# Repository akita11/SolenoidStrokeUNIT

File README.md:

# SolenoidStokeUNIT

ソレノイドのストローク位置によってインダクタンスが変化し、PWM制御時の電流波形が変化することを利用して、ソレノイドのPWM制御とストローク位置の計測（推定）を同時に行うための回路です。

**【注意：重要】**
実際の制御・計測の動作には、ソレノイドごとに特性の計測を行う必要があり、また特性の個体差、温度特性なども考慮する必要があります。そのため、**「これを使ってサンプルプログラムを書き込めば間違いなく動作する（制御ができる）」というものではなく、あくまでもこの原理検証の実験のための回路**ということをご理解ください。測定原理やサンプルプログラムは[こちら](https://github.com/akita11/SolenoidStrokeMeasureControl)に適宜まとめて更新していきます。

## 使い方

オレンジ色のコネクタ(VH3.96-4p)に、ソレノイド用の電源とソレノイドを接続します。M5Stackの[BAVGソケット](https://www.switch-science.com/products/7234)を使うと、電源は2.1mmプラグ、負荷はスプリング端子で接続できて便利です。

Grove端子にUART通信元（M5Stack等のマイコンやUSBシリアル変換器）を接続し、本UNITに対してコマンド送信や結果の受信を行います。Grove端子の信号は、"RXD(受信) / TXD(送信) / VDD(+5V) / GND"の順です。ここでRXDとTXDの「主語」は本UNITです。つまり本UNITの"RXD"は、UART送信元の送信(TX)に接続します。（なおM5StackのPortCのTX/RXはこの順序ですのでそのまま接続できます）

### コマンド

コマンドは、基本的に、「コマンドを表す1文字 + 引数（10進数表記：ないものもある） + <CR> or <LF>」の形式です。各コマンドの成功時には'S'と'P'以外では指定された設定が返され、定義されていないコマンドでは'?'が返されます。

- 'S' : 測定開始（引数なし）：後述の形式で測定データが送出されます
- 'P' : 測定停止（引数なし）
- 'D' : PWM ON時間の設定（引数：PWM ON時間（単位は0.8us））
- 'T' : PWM ON時間の設定（引数：PWM周期（単位は0.8us））
- '0' : PWM ONから第1サンプリング点までの時間（引数：PWM周期（単位は0.8us））
- '1' : PWM ONから第2サンプリング点までの時間（引数：PWM周期（単位は0.8us））
- 'C' : 内部蓄積回数（引数：回）

### 送出データの形式

AAAABBBB + <CR> + <LF>

- AAAA : 第1サンプリング点の電圧値（10進数4桁）：0=0V, 1023=5V
- BBBB : 第2サンプリング点の電圧値（10進数4桁）：0=0V, 1023=5V

### 増幅率の調整

ソレノイドの駆動電流を0.2Ωの抵抗で電圧変換し、それをオペアンプ（非反転増幅回路）で増幅して"ADC"端子に出力しています。その増幅率は、用いるソレノイド・電源電圧からきまる駆動電流にあわせて、適切な範囲に調整する必要があります。"ADC"端子の波形をオシロ等で計測し、用いるマイコンのADCの入力電圧範囲に収まるように増幅率を調整します。増幅率は基板裏面のハンダジャンパJP3/JP4JP5で調整できます。（JP3は初期状態でONになっていますので、OFFにする場合はパターンをカットしてください）

- JP3/JP4/JP5=ON/OFF/OFF : 101倍
- JP3/JP4/JP5=ON/ON/OFF : 39倍
- JP3/JP4/JP5=ON/OFF/ON : 20倍
- JP3/JP4/JP5=ON/ON/ON : 16倍
- JP3/JP4/JP5=OFF/OFF/OFF : R1にとりつける抵抗から決まる倍率（(R1÷1[kΩ]+1)倍）

## 測定原理

ソレノイドは電気回路的にはインダクタで、そのインダクタンスはストローク（プランジャ）位置で変化します。そのためON時の充電電流の波形は、ストローク位置で変化します。ただし充電開始時の電流はOFF期間中の放電特性できまるため、ゼロからとは限りません。またPWMのON時間（PWMのデューティー比）によっても波形は変化します。

ソレノイドによっては、ON後の2箇所の時点（例えば100us後と700us後）での電流の差が、PWMのON時間（PWMのデューティー比）ごとにストローク位置に伴って変化するため、与えているPWM ON時間とその電流差から、ストローク位置を計測（推定）することができます。具体的には、PWM ON後に電流が徐々に増加するところの2点（第1・第2サンプリング点）の電圧から、あらかじめ学習させた深層学習CNNモデルによってソレノイドのストローク位置とコイル温度を求めることができます。詳細はarXivの[論文(1)](https://arxiv.org/abs/2405.11721)と[論文(2)](https://arxiv.org/abs/2411.07270)にまとめてあります。

ただしソレノイドによっては、この電流差がストロークによってほとんど変化しないため、この方法では位置を計測することができません。そのため、複数点の電流の計測値から、予め計測した位置と電流値との差（の総和）が最小となるように反復計算で位置を求めるアルゴリズムを開発中です。まだ安定性や精度の検証は不十分ですが、参考用に上記GitHubにいくつかのソレノイドのCNNモデルと、それをESP32(M5Stack等)で実行するためのソースコードをおいてあります。

現在、SSBH-0830-02用の推定モデルとそれを使った位置制御(Control_ESP32/)をおいてあります。上記GitHubの生活をREADME.mdは別の計測制御(SolenoidStokeMeasureControlUNIT)用の情報が書いてありますが、この位置制御のソースコードは、本ユニット用のものです。

## Author

Junichi Akita (akita@ifdl.jp, @akita11)

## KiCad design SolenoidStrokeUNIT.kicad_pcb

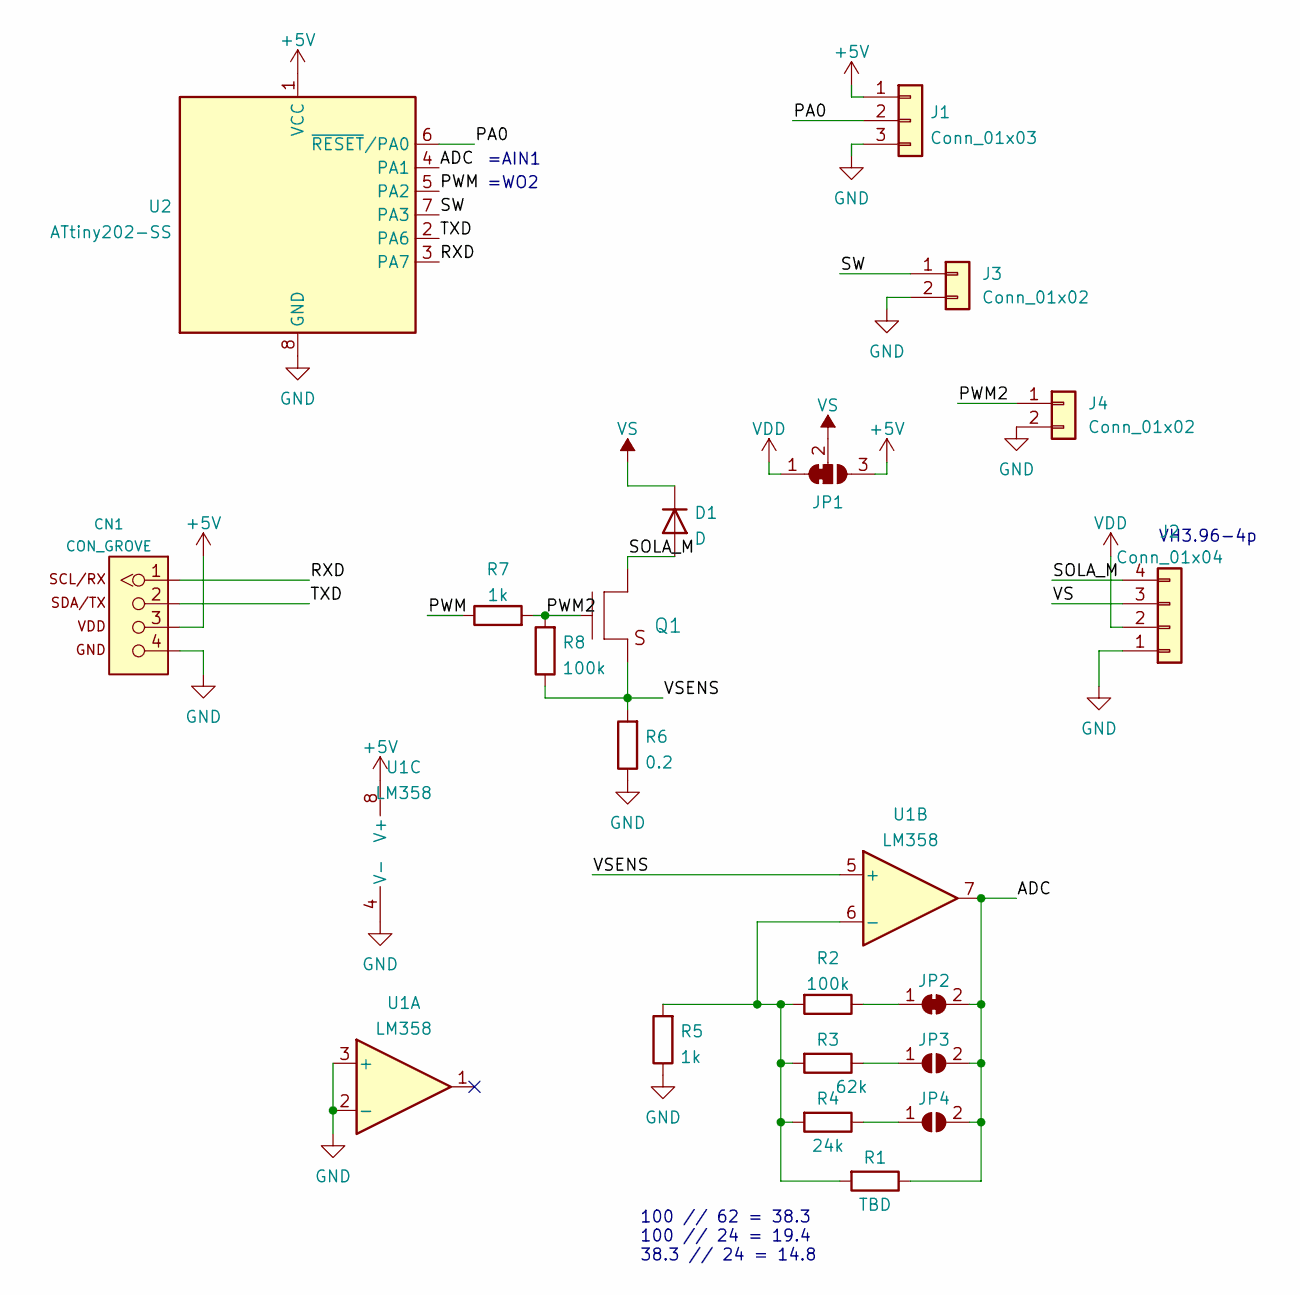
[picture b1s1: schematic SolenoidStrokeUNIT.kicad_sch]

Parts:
CN1: CON_GROVE; CON_GROVE_H
D1: D; D_SOD-123F
J1: Conn_01x03; PinSocket_1x03_P2.54mm_Vertical
J2: Conn_01x04; JST_VH_S4P-VH_1x04_P3.96mm_Horizontal
J3, J4: Conn_01x02; PinSocket_1x02_P2.54mm_Vertical
JP1: SolderJumper_3_Bridged12; SolderJumper-3_P1.3mm_Bridged2Bar12_Pad1.0x1.5mm
JP2: SolderJumper_2_Bridged; SolderJumper-2_P1.3mm_Bridged_Pad1.0x1.5mm
JP3, JP4: SolderJumper_2_Open; SolderJumper-2_P1.3mm_Open_Pad1.0x1.5mm
Q1: TR_NMOS_IRLML6344; SOT-23
R1: TBD; R_Axial_DIN0207_L6.3mm_D2.5mm_P2.54mm_Vertical
R2, R8: 100k; R_0603_1608Metric
R3: 62k; R_0603_1608Metric
R4: 24k; R_0603_1608Metric
R5, R7: 1k; R_0603_1608Metric
R6: 0.2; R_1206_3216Metric
U1: LM358; SO-8_3.9x4.9mm_P1.27mm
U2: ATtiny202-SS; SOIC-8_3.9x4.9mm_P1.27mm

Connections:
+5V: CN1.3, J1.1, JP1.3 (B), U1.8 (V+), U2.1 (VCC)
/ADC: JP2.2 (B), JP3.2 (B), JP4.2 (B), R1.1, U1.7, U2.4 (PA1)
/PA0: J1.2, U2.6 (~RESET/PA0)
/PWM: R7.1, U2.5 (PA2)
/PWM2: J4.1, Q1.1 (G), R7.2, R8.2
/RXD: CN1.1, U2.3 (PA7)
/SOLA_M: D1.2 (A), J2.4, Q1.3 (D)
/SW: J3.1, U2.7 (PA3)
/TXD: CN1.2, U2.2 (PA6)
/VSENS: Q1.2 (S), R6.2, R8.1, U1.5 (+)
GND: CN1.4, J1.3, J2.1, J3.2, J4.2, R5.1, R6.1, U1.2 (-), U1.3 (+), U1.4 (V-), U2.8 (GND)
unnamed: JP2.1 (A), R2.1
unnamed: JP3.1 (A), R3.1
unnamed: JP4.1 (A), R4.1
unnamed: R1.2, R2.2, R3.2, R4.2, R5.2, U1.6 (-)
VDD: J2.2, JP1.1 (A)
VS: D1.1 (K), J2.3, JP1.2 (C)

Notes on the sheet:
100 // 62 = 38.3 100 // 24 = 19.4 38.3 // 24 = 14.8
=WO2
VH3.96-4p
=AIN1

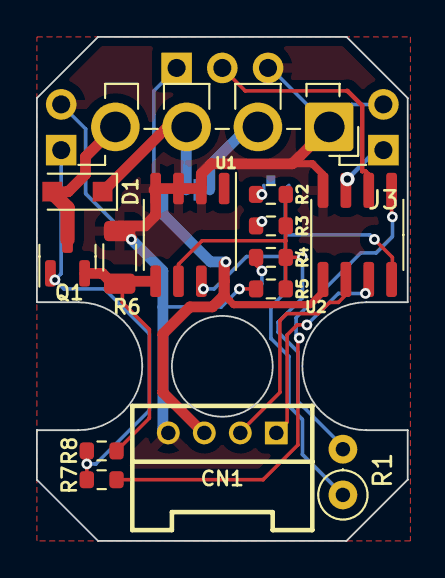
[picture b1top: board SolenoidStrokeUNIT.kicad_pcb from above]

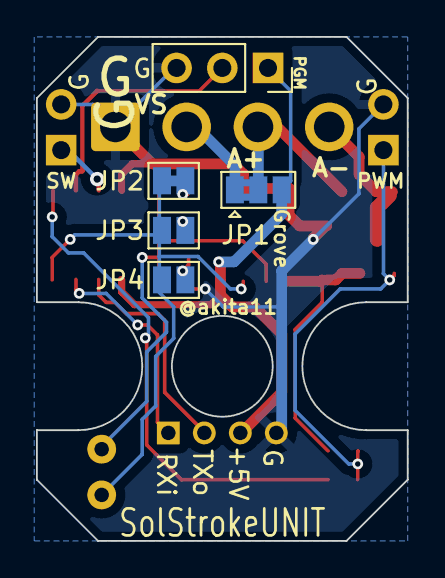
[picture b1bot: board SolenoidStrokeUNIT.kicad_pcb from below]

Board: 2 copper layers, 20.6 x 28.0 mm, 21 parts (5 on the bottom side), 17 nets.

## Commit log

2024-12-25 tentative initial commit
2024-12-25 typo in README fix
